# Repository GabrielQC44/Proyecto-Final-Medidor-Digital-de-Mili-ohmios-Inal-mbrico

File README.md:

# Medidor Digital de Mili-ohmios Inalámbrico (IoT)

**Proyecto Final – Diseño de Sistemas Electrónicos**  
*Escuela de Ingenierías Eléctrica, Electrónica y de Telecomunicaciones (E3T)*  
**Universidad Industrial de Santander (UIS)**  
**Grupo:** C1B-A1A  

---

## Autores
* **Gabriel Camilo Quijano Celis** – *Código:* 2192312
* **Carlos Daniel Aguilera Iglesias** – *Código:* 2192318

---

## Descripción del Proyecto

El **Medidor Digital de Mili-ohmios Inalámbrico** es un instrumento de metrología portátil diseñado para medir resistencias de ultra-bajo valor en el rango de **$0.5\,\text{m}\Omega$ a $1000\,\text{m}\Omega$**. 

Fundamentado en el **método de cuatro hilos (Conexión Kelvin)** y **medición ratiométrica**, elimina por completo los errores introducidos por resistencias parásitas de cables, conectores y derivas térmicas por efecto Seebeck. Los datos metrológicos se procesan mediante un microcontrolador ESP32-C3 SuperMini y se transmiten vía **Bluetooth Low Energy (BLE 5)** hacia una interfaz web responsiva e interactiva.

---

## Probar la Aplicación Web (Sin Descargas)

Puedes probar e interactuar con la interfaz gráfica del instrumento directamente desde tu navegador sin instalar nada:  
**[Abrir Aplicación en GitHub Pages](https://gabrielqc44.github.io/Proyecto-Final-Medidor-Digital-de-Mili-ohmios-Inal-mbrico/)**

---

## Arquitectura del Hardware

El hardware se divide en cuatro etapas funcionales integradas en una placa de $7 \times 7\,\text{cm}$:

1. **Etapa 1: Gestión de Alimentación y Carga:** Módulo TP4056 con protección BMS para batería Li-Po 1S y regulador Buck-Boost TPS63802 ($3.3\,\text{V}$ estables).
2. **Etapa 2: Fuente de Corriente Constante y Escalas:** Lazo analógico de precisión (OPA376 + MOSFET IRLZ44N) accionado por un buffer 74LVC1G125 mediante excitación pulsada de $55\,\text{ms}$ ($100\,\text{mA}$, $500\,\text{mA}$ y $1\,\text{A}$).
3. **Etapa 3: Adquisición Analógica de Alta Precisión:** Convertidor $\Delta-\Sigma$ ADS1220 de 24 bits configurado en modo diferencial ratiométrico.
4. **Etapa 4: Control y Comunicaciones:** Microcontrolador ESP32-C3 SuperMini ejecutando el servidor BLE GATT y algoritmos de *Auto-Zeroing* (compensación ON/OFF).

---

## Estructura del Repositorio

| Archivo / Carpeta | Descripción |
| :--- | :--- |
| `esquemas/` | Planos esquemáticos del circuito impreso y documentación técnica. |
| `gerbers/` | Archivos de fabricación Gerber para la manufactura de la placa PCB. |
| `Aplicacion.apk` | Instalador compilado para dispositivos móviles Android. |
| `Codigo_ESP.txt` | Código fuente del firmware en C++ para el microcontrolador ESP32-C3. |
| `Interfazz.html` | Código fuente de la interfaz gráfica web en HTML5, CSS3 y JavaScript. |
| `index.html` | Despliegue de la interfaz web para el servidor de GitHub Pages. |
| `logo.png` | Logotipo oficial e identidad visual del proyecto. |

---

## Características Clave
* **Modo Ratiométrico:** Inmune a fluctuaciones o derivas en la corriente de excitación.
* **Excitación Pulsada ($<10\%$ Ciclo de Trabajo):** Disipa menos de $0.41\,\text{W}$, evitando autocalentamiento en resistencias SMD 2512.
* **Compensación de Offset:** Técnica de dos fases ($V_{\text{ON}} - V_{\text{OFF}}$) que anula tensiones termoeléctricas.
* **Costo-Efectivo:** Construcción total por **$20.40 USD** (~$88\%$ de ahorro frente a equipos comerciales equivalentes).

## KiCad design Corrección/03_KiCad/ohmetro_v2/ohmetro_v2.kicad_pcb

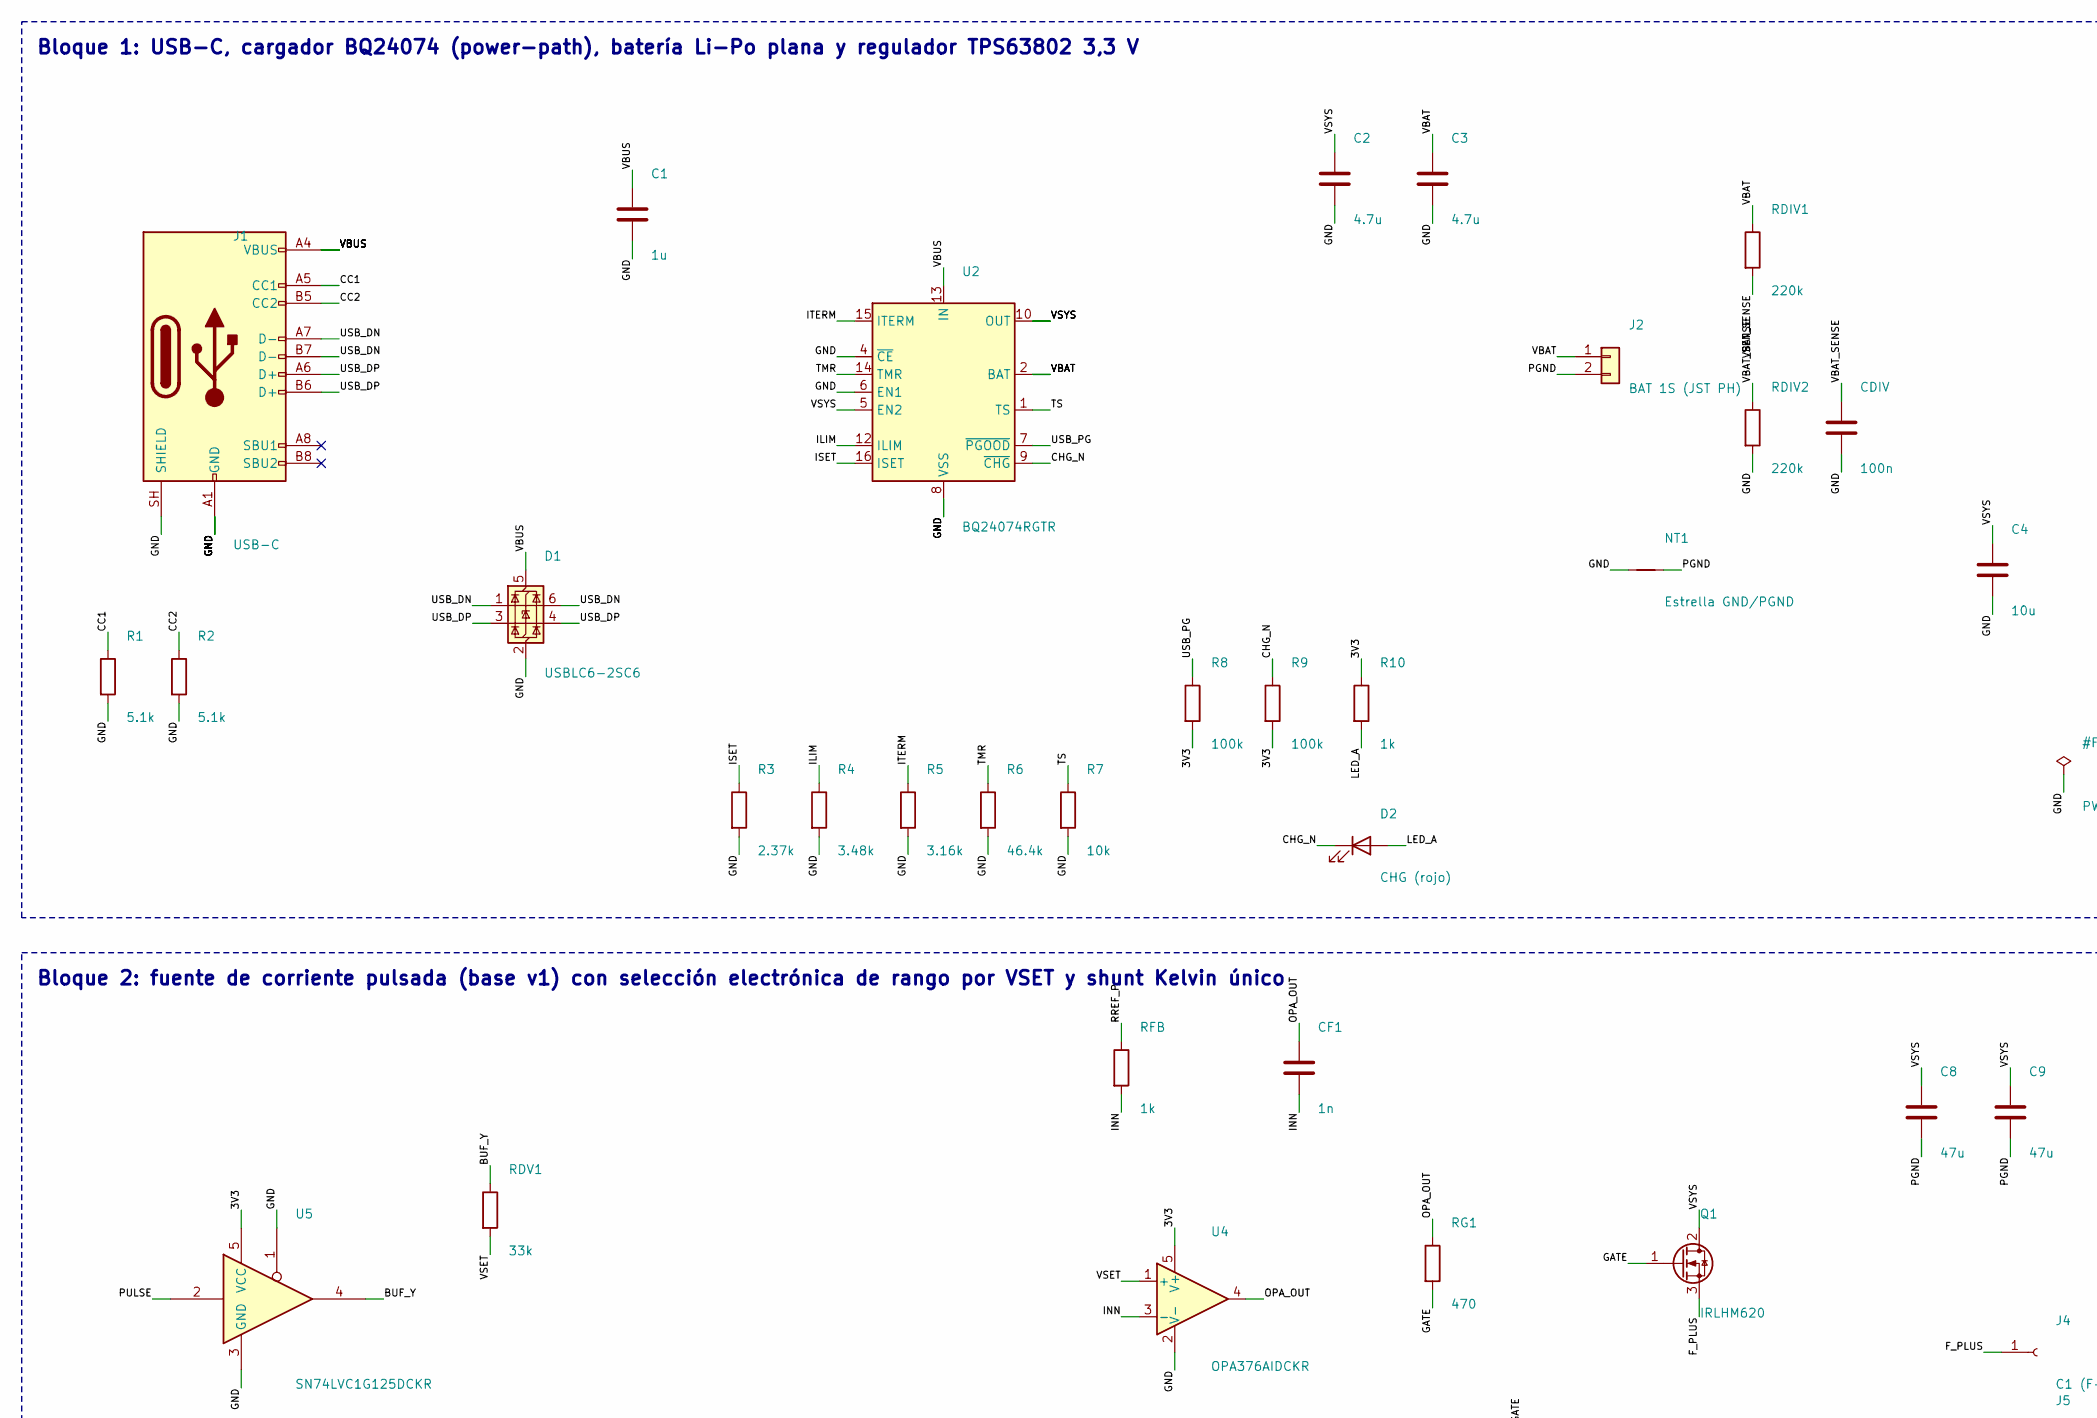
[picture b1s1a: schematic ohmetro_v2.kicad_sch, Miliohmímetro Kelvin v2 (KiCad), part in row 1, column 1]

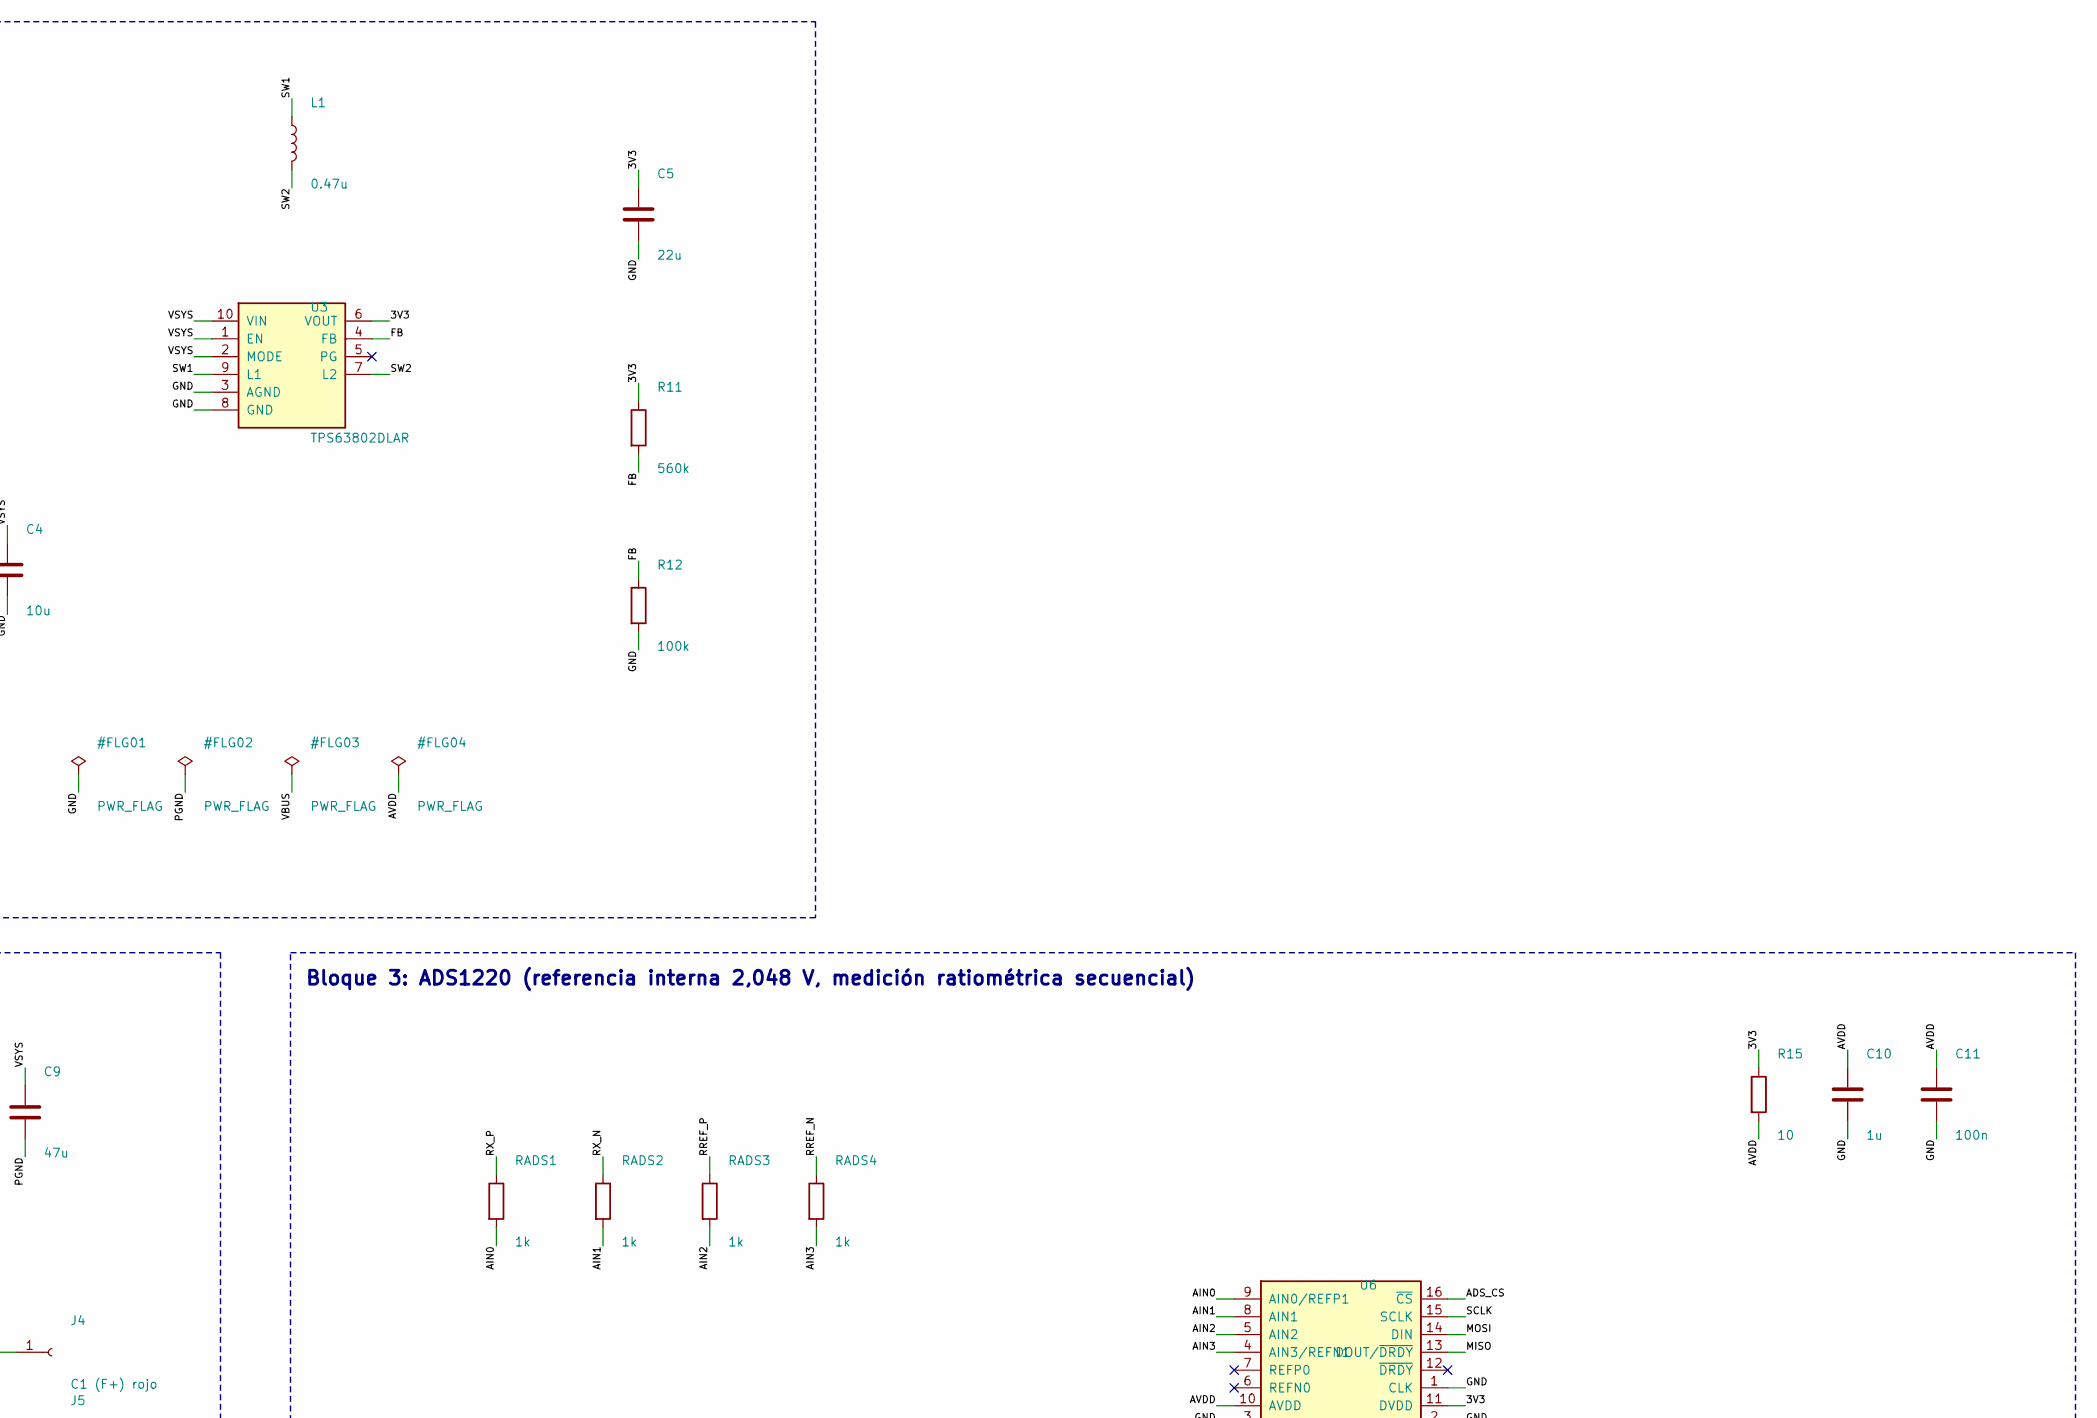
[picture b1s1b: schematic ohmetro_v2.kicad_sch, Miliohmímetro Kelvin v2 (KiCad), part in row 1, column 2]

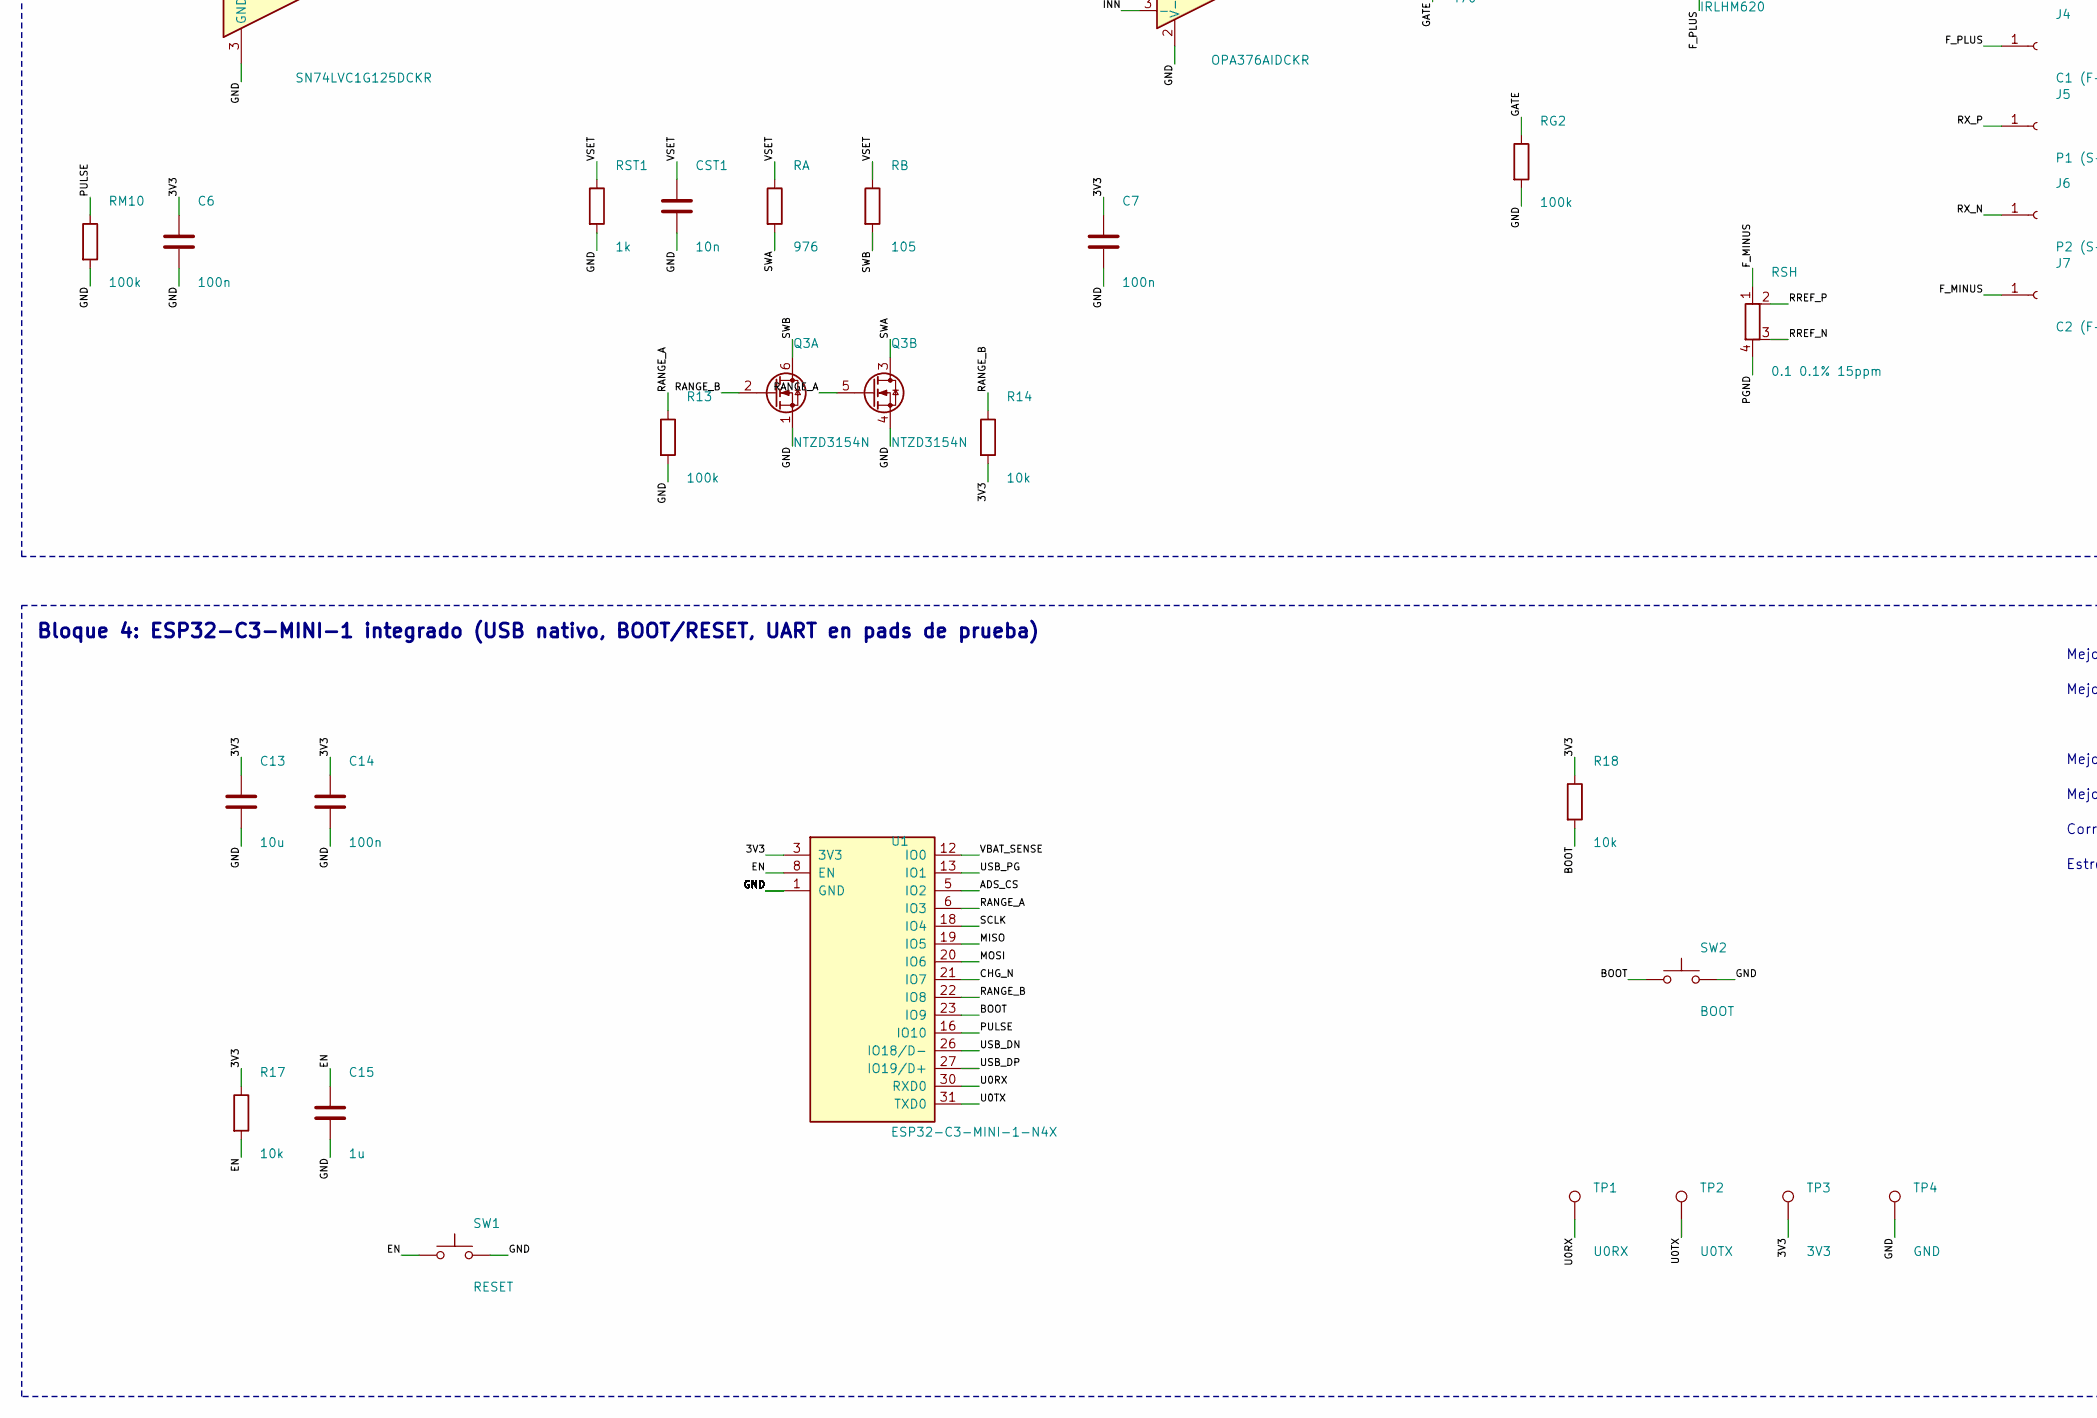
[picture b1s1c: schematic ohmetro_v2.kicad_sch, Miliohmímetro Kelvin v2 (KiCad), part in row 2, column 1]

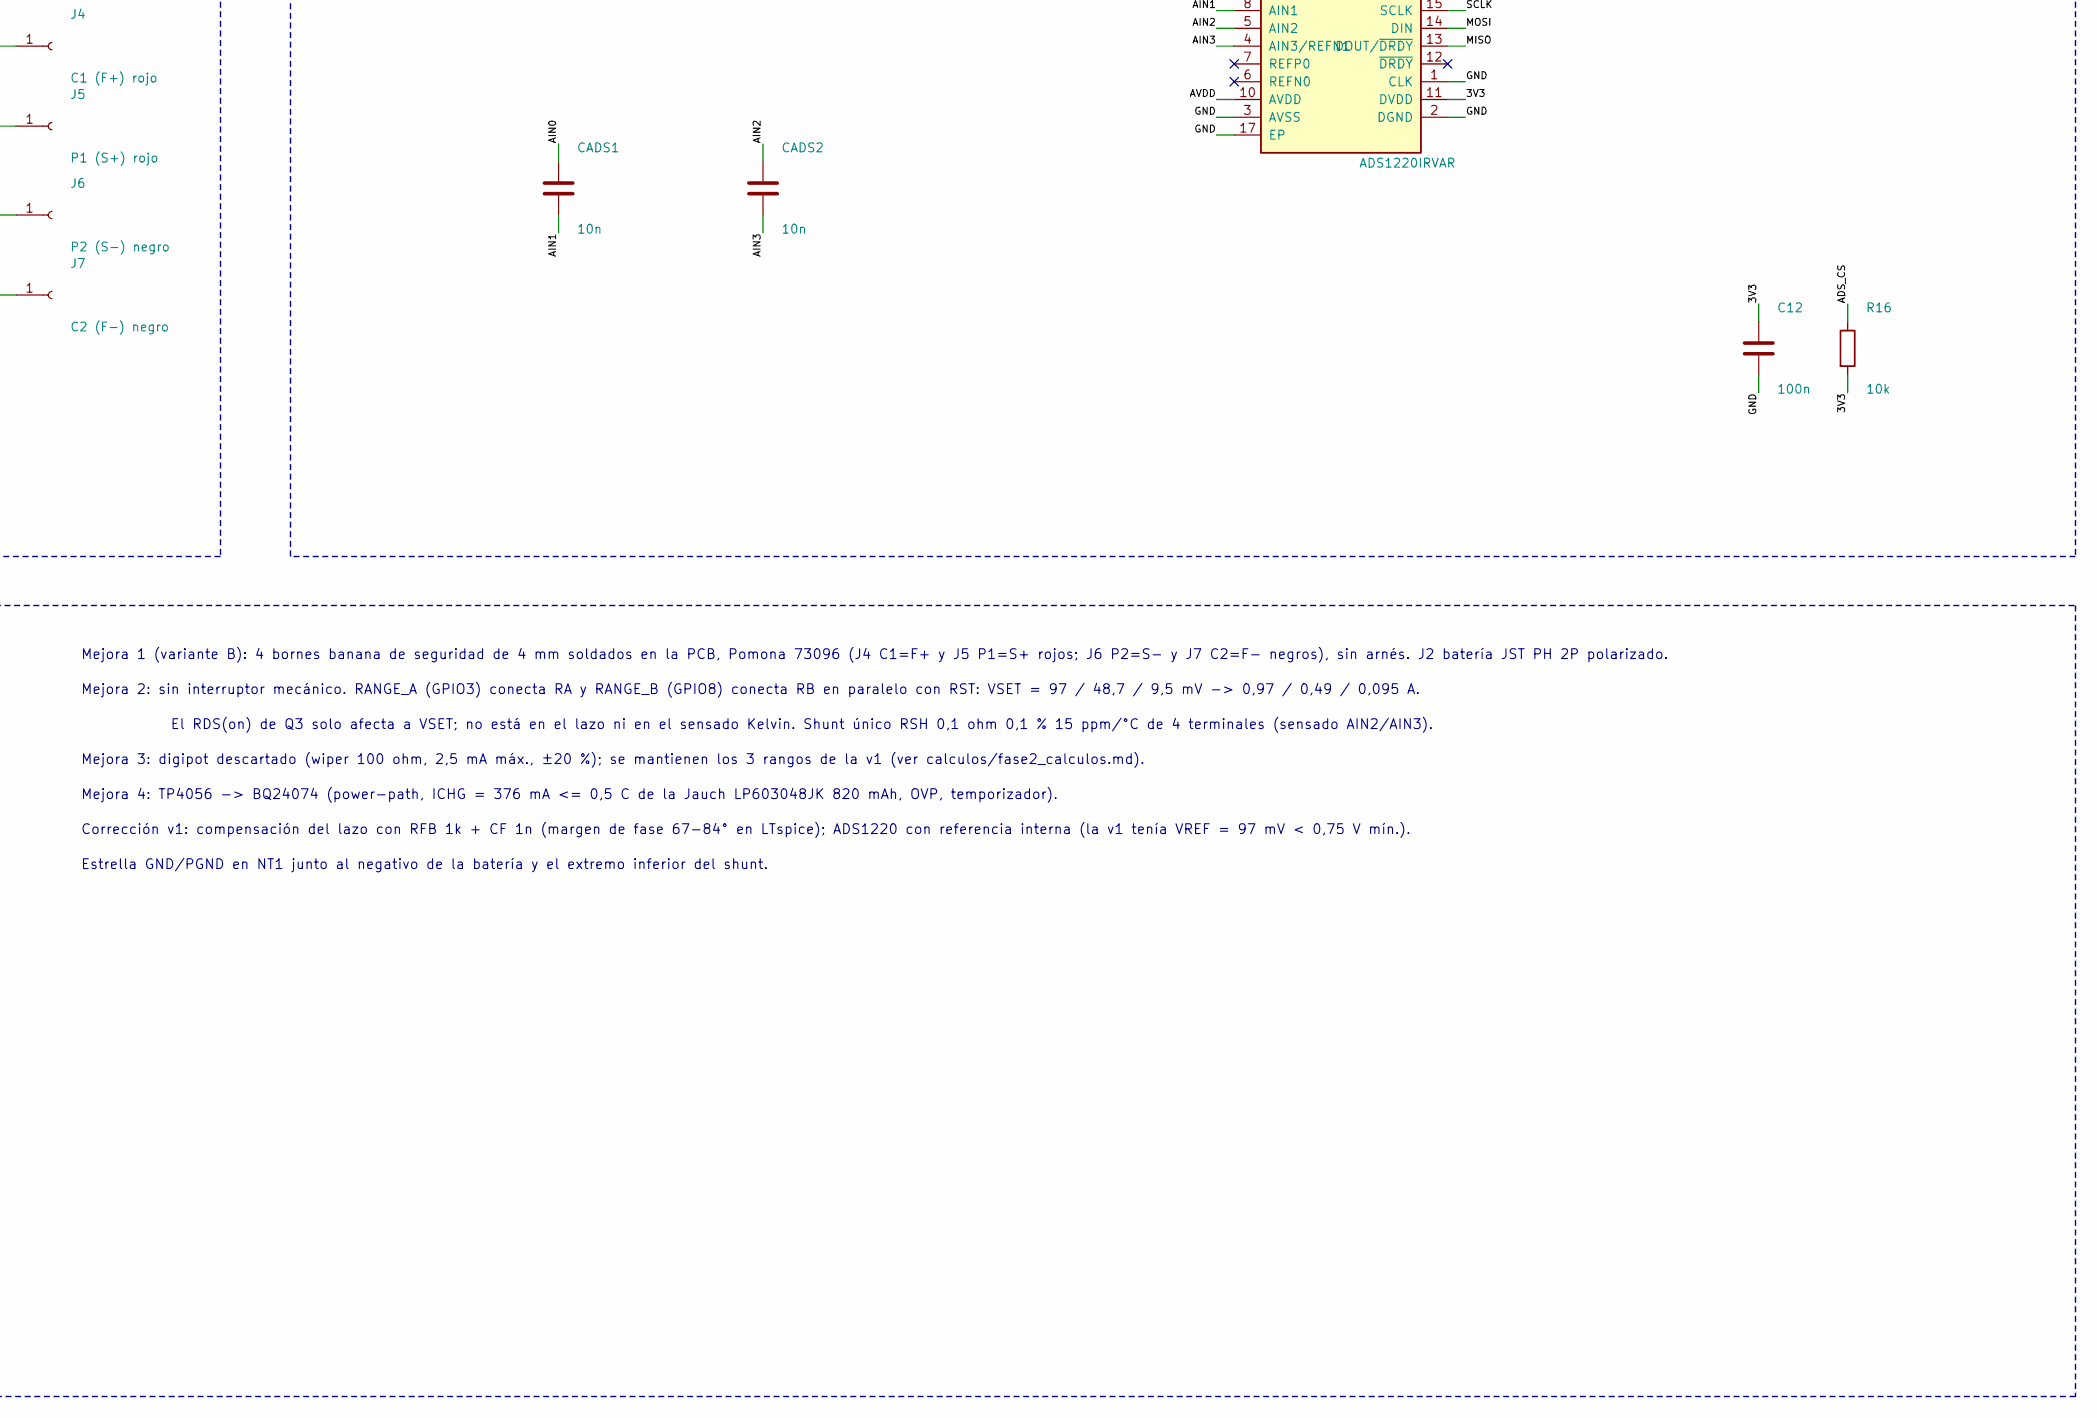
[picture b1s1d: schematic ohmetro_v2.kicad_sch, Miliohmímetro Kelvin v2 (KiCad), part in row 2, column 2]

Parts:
C1, C10, C15: 1u; C_0402_1005Metric; MPN CL05A105KA5NQNC
C2, C3: 4.7u; C_0603_1608Metric; MPN CL10A475KO8NNNC
C4, C13: 10u; C_0603_1608Metric; MPN CL10A106KP8NNNC
C5: 22u; C_0805_2012Metric; MPN GRM21BR61A226ME44L
C6, C7, C11, C12, C14: 100n; C_0402_1005Metric; MPN CL05B104KO5NNNC
C8, C9: 47u; C_0805_2012Metric; MPN CL21A476MQYNNNE
CADS1, CADS2: 10n; C_0603_1608Metric; MPN GRM1885C1H103JA01D
CDIV: 100n; C_0402_1005Metric; MPN CL05B104KO5NNNC
CF1: 1n; C_0402_1005Metric; MPN GRM1555C1H102JA01D
CST1: 10n; C_0603_1608Metric; MPN GRM1885C1H103JA01D
D1: USBLC6-2SC6; SOT-23-6; MPN USBLC6-2SC6
D2: CHG (rojo); LED_0603_1608Metric; MPN LTST-C191KRKT
J1: USB-C; USB_C_Receptacle_GCT_USB4105-xx-A_16P_TopMnt_Horizontal; MPN USB4105-GF-A
J2: BAT 1S (JST PH); JST_PH_S2B-PH-SM4-TB_1x02-1MP_P2.00mm_Horizontal; MPN S2B-PH-SM4-TB(LF)(SN)
J4: C1 (F+) rojo; Pomona_73096_4mm_Vertical; MPN 73096-2
J5: P1 (S+) rojo; Pomona_73096_4mm_Vertical; MPN 73096-2
J6: P2 (S-) negro; Pomona_73096_4mm_Vertical; MPN 73096-0
J7: C2 (F-) negro; Pomona_73096_4mm_Vertical; MPN 73096-0
L1: 0.47u; L_Murata_DFE201610P; MPN DFE201612E-R47M=P2
NT1: Estrella GND/PGND; NetTie-2_SMD_Pad0.5mm
Q1: IRLHM620; Infineon_PQFN-8_3.3x3.3mm; MPN IRLHM620TRPBF
Q3: NTZD3154N; SOT-563; MPN NTZD3154NT1G
R1, R2: 5.1k; R_0402_1005Metric; MPN RC0402FR-075K1L
R3: 2.37k; R_0402_1005Metric; MPN RC0402FR-072K37L
R4: 3.48k; R_0402_1005Metric; MPN RC0402FR-073K48L
R5: 3.16k; R_0402_1005Metric; MPN RC0402FR-073K16L
R6: 46.4k; R_0402_1005Metric; MPN RC0402FR-0746K4L
R7, R14, R16, R17, R18: 10k; R_0402_1005Metric; MPN RC0402FR-0710KL
R8, R9, R12, R13: 100k; R_0402_1005Metric; MPN RC0402FR-07100KL
R10: 1k; R_0402_1005Metric; MPN RC0402FR-071KL
R11: 560k; R_0402_1005Metric; MPN RC0402FR-07560KL
R15: 10; R_0402_1005Metric; MPN RC0402FR-0710RL
RA: 976; R_0402_1005Metric; MPN RC0402FR-07976RL
RADS1, RADS2, RADS3, RADS4: 1k; R_0402_1005Metric; MPN ERA-2AEB102X
RB: 105; R_0402_1005Metric; MPN RC0402FR-07105RL
RDIV1, RDIV2: 220k; R_0402_1005Metric; MPN RC0402FR-07220KL
RDV1: 33k; R_0402_1005Metric; MPN RC0402FR-0733KL
RFB: 1k; R_0402_1005Metric; MPN RC0402FR-071KL
RG1: 470; R_0402_1005Metric; MPN RC0402FR-07470RL
RG2: 100k; R_0402_1005Metric; MPN RC0402FR-07100KL
RM10: 100k; R_0402_1005Metric; MPN RC0402FR-07100KL
RSH: 0.1 0.1% 15ppm; R_Shunt_VPG_CSM2512S_4T; MPN Y44870R10000B9R
RST1: 1k; R_0402_1005Metric; MPN RC0402FR-071KL
SW1: RESET; SW_SPST_PTS810; MPN PTS815SJM250SMTRLFS
SW2: BOOT; SW_SPST_PTS810; MPN PTS815SJM250SMTRLFS
TP1: U0RX; TestPoint_Pad_D1.0mm
TP2: U0TX; TestPoint_Pad_D1.0mm
TP3: 3V3; TestPoint_Pad_D1.0mm
TP4: GND; TestPoint_Pad_D1.0mm
U1: ESP32-C3-MINI-1-N4X; ESP32-C3-MINI-1; MPN ESP32-C3-MINI-1-N4X
U2: BQ24074RGTR; VQFN-16-1EP_3x3mm_P0.5mm_EP1.68x1.68mm_ThermalVias; MPN BQ24074RGTR
U3: TPS63802DLAR; TI_DLA_VSON-HR-10_2x3mm; MPN TPS63802DLAR
U4: OPA376AIDCKR; SOT-353_SC-70-5; MPN OPA376AIDCKR
U5: SN74LVC1G125DCKR; SOT-353_SC-70-5; MPN SN74LVC1G125DCKR
U6: ADS1220IRVAR; Texas_RVA_VQFN-16-1EP_3.5x3.5mm_P0.5mm_EP2.14x2.14mm; MPN ADS1220IRVAR

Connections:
/3V3: C5.1, C6.1, C7.1, C12.1, C13.1, C14.1, R8.2, R9.2, R10.1, R11.1, R14.2, R15.1, R16.2, R17.1, R18.1, TP3.1, U1.3 (3V3), U3.6 (VOUT), U4.5 (V+), U5.5 (VCC), U6.11 (DVDD)
/ADS_CS: R16.1, U1.5 (IO2), U6.16 (~CS)
/AIN0: CADS1.1, RADS1.2, U6.9 (AIN0/REFP1)
/AIN1: CADS1.2, RADS2.2, U6.8 (AIN1)
/AIN2: CADS2.1, RADS3.2, U6.5 (AIN2)
/AIN3: CADS2.2, RADS4.2, U6.4 (AIN3/REFN1)
/AVDD: C10.1, C11.1, R15.2, U6.10 (AVDD)
/BOOT: R18.2, SW2.1, U1.23 (IO9)
/BUF_Y: RDV1.1, U5.4
/CC1: J1.A5 (CC1), R1.1
/CC2: J1.B5 (CC2), R2.1
/CHG_N: D2.1 (K), R9.1, U1.21 (IO7), U2.9 (~CHG)
/EN: C15.1, R17.2, SW1.1, U1.8 (EN)
/FB: R11.2, R12.1, U3.4 (FB)
/F_MINUS: J7.1, RSH.1
/F_PLUS: J4.1, Q1.3 (S)
/GATE: Q1.1 (G), RG1.2, RG2.1
/ILIM: R4.1, U2.12 (ILIM)
/INN: CF1.2, RFB.2, U4.3 (-)
/ISET: R3.1, U2.16 (ISET)
/ITERM: R5.1, U2.15 (ITERM)
/LED_A: D2.2 (A), R10.2
/MISO: U1.19 (IO5), U6.13 (DOUT/~DRDY)
/MOSI: U1.20 (IO6), U6.14 (DIN)
/OPA_OUT: CF1.1, RG1.1, U4.4
/PGND: C8.2, C9.2, J2.2, NT1.2, RSH.4
/PULSE: RM10.1, U1.16 (IO10), U5.2
/RANGE_A: Q3.5 (G), R13.1, U1.6 (IO3)
/RANGE_B: Q3.2 (G), R14.1, U1.22 (IO8)
/RREF_N: RADS4.1, RSH.3
/RREF_P: RADS3.1, RFB.1, RSH.2
/RX_N: J6.1, RADS2.1
/RX_P: J5.1, RADS1.1
/SCLK: U1.18 (IO4), U6.15 (SCLK)
/SW1: L1.1, U3.9 (L1)
/SW2: L1.2, U3.7 (L2)
/SWA: Q3.3 (D), RA.2
/SWB: Q3.6 (D), RB.2
/TMR: R6.1, U2.14 (TMR)
/TS: R7.1, U2.1 (TS)
/U0RX: TP1.1, U1.30 (RXD0)
/U0TX: TP2.1, U1.31 (TXD0)
/USB_DN: D1.1 (I/O1), D1.6 (I/O1), J1.A7 (D-), J1.B7 (D-), U1.26 (IO18/D-)
/USB_DP: D1.3 (I/O2), D1.4 (I/O2), J1.A6 (D+), J1.B6 (D+), U1.27 (IO19/D+)
/USB_PG: R8.1, U1.13 (IO1), U2.7 (~PGOOD)
/VBAT: C3.1, J2.1, RDIV1.1, U2.2 (BAT), U2.3 (BAT)
/VBAT_SENSE: CDIV.1, RDIV1.2, RDIV2.1, U1.12 (IO0)
/VBUS: C1.1, D1.5 (VBUS), J1.A4 (VBUS), J1.A9 (VBUS), J1.B4 (VBUS), J1.B9 (VBUS), U2.13 (IN)
/VSET: CST1.1, RA.1, RB.1, RDV1.2, RST1.1, U4.1 (+)
/VSYS: C2.1, C4.1, C8.1, C9.1, Q1.2 (D), U2.5 (EN2), U2.10 (OUT), U2.11 (OUT), U3.1 (EN), U3.2 (MODE), U3.10 (VIN)
GND: C1.2, C2.2, C3.2, C4.2, C5.2, C6.2, C7.2, C10.2, C11.2, C12.2, C13.2, C14.2, C15.2, CDIV.2, CST1.2, D1.2 (GND), J1.A1 (GND), J1.A12 (GND), J1.B1 (GND), J1.B12 (GND), J1.SH (SHIELD), NT1.1, Q3.1 (S), Q3.4 (S), R1.2, R2.2, R3.2, R4.2, R5.2, R6.2, R7.2, R12.2, R13.2, RDIV2.2, RG2.2, RM10.2, RST1.2, SW1.2, SW2.2, TP4.1, U1.1 (GND), U1.2 (GND), U1.11 (GND), U1.14 (GND), U1.36 (GND), U1.37 (GND), U1.38 (GND), U1.39 (GND), U1.40 (GND), U1.41 (GND), U1.42 (GND), U1.43 (GND), U1.44 (GND), U1.45 (GND), U1.46 (GND), U1.47 (GND), U1.48 (GND), U1.49 (GND), U1.50 (GND), U1.51 (GND), U1.52 (GND), U1.53 (GND), U2.4 (~CE), U2.6 (EN1), U2.8 (VSS), U2.17 (VSS), U3.3 (AGND), U3.8 (GND), U4.2 (V-), U5.1, U5.3 (GND), U6.1 (CLK), U6.2 (DGND), U6.3 (AVSS), U6.17 (EP)

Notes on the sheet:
Bloque 1: USB-C, cargador BQ24074 (power-path), batería Li-Po plana y regulador TPS63802 3,3 V
Bloque 2: fuente de corriente pulsada (base v1) con selección electrónica de rango por VSET y shunt Kelvin único
Bloque 3: ADS1220 (referencia interna 2,048 V, medición ratiométrica secuencial)
Bloque 4: ESP32-C3-MINI-1 integrado (USB nativo, BOOT/RESET, UART en pads de prueba)
Mejora 1 (variante B): 4 bornes banana de seguridad de 4 mm soldados en la PCB, Pomona 73096 (J4 C1=F+ y J5 P1=S+ rojos; J6 P2=S- y J7 C2=F- negros), sin arnés. J2 batería JST PH 2P polarizado.
Mejora 2: sin interruptor mecánico. RANGE_A (GPIO3) conecta RA y RANGE_B (GPIO8) conecta RB en paralelo con RST: VSET = 97 / 48,7 / 9,5 mV -> 0,97 / 0,49 / 0,095 A.
El RDS(on) de Q3 solo afecta a VSET; no está en el lazo ni en el sensado Kelvin. Shunt único RSH 0,1 ohm 0,1 % 15 ppm/°C de 4 terminales (sensado AIN2/AIN3).
Mejora 3: digipot descartado (wiper 100 ohm, 2,5 mA máx., ±20 %); se mantienen los 3 rangos de la v1 (ver calculos/fase2_calculos.md).
Mejora 4: TP4056 -> BQ24074 (power-path, ICHG = 376 mA <= 0,5 C de la Jauch LP603048JK 820 mAh, OVP, temporizador).
Corrección v1: compensación del lazo con RFB 1k + CF 1n (margen de fase 67-84° en LTspice); ADS1220 con referencia interna (la v1 tenía VREF = 97 mV < 0,75 V mín.).
Estrella GND/PGND en NT1 junto al negativo de la batería y el extremo inferior del shunt.

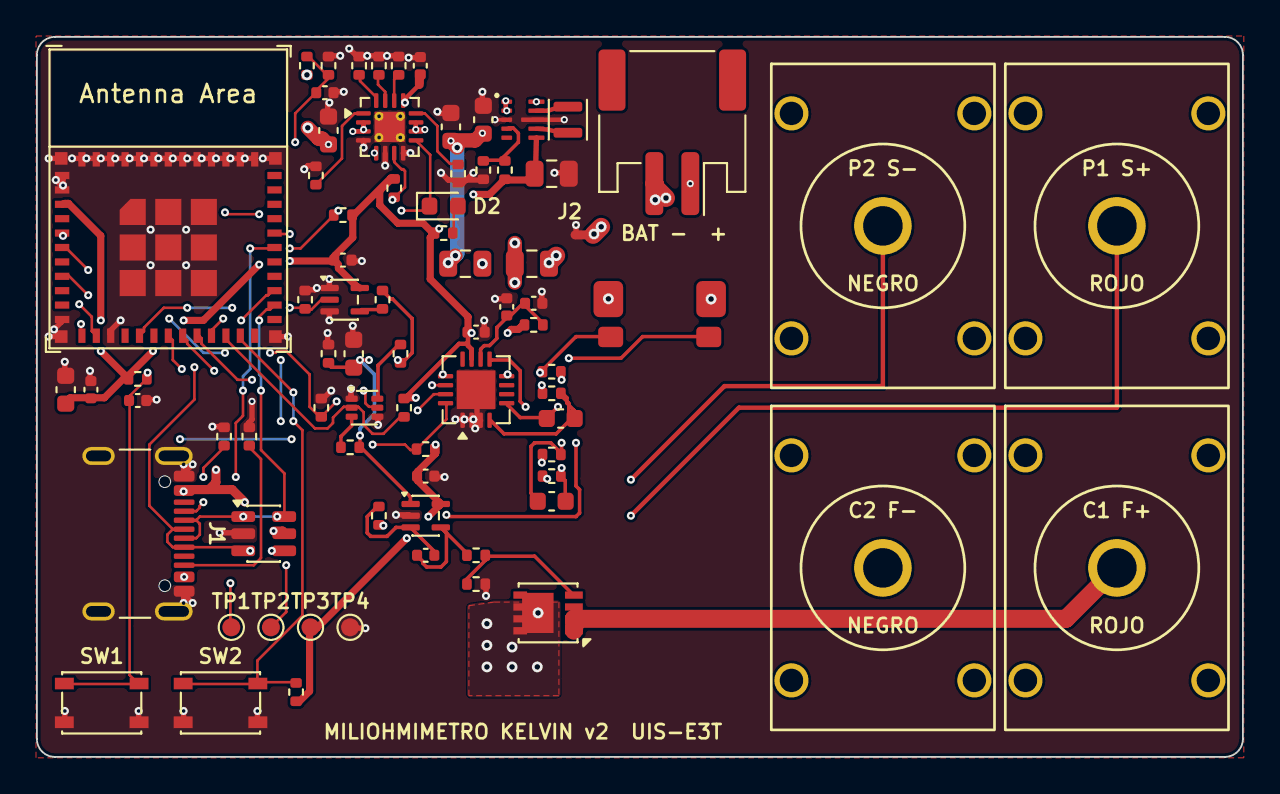
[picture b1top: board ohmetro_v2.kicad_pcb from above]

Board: 4 copper layers, 67.0 x 40.0 mm, 77 parts (0 on the bottom side), 51 nets.

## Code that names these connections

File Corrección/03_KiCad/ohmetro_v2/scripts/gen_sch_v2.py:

# -*- coding: utf-8 -*-
"""Genera ohmetro_v2.kicad_sch (mejoras 1–4 y ESP32-C3-MINI-1 integrado) y la biblioteca ohmetro.kicad_sym."""
import os, sys
HERE = os.path.dirname(os.path.abspath(__file__))
sys.path.insert(0, HERE); sys.path.insert(0, os.path.join(HERE, "..", "..", "tools"))
from kicad_sch_lib import Sheet, flat_symbol
import design_v2 as D

OUT = os.path.join(HERE, "..")

def sym_box(name, left, right, ref="U", width=20.32, stack_names=("GND",)):
    """Símbolo rectangular; pines con nombre en stack_names se apilan (uno visible)."""
    def side(lst, x, ang):
        out, slot, stacked = [], 0, {}
        for num, nm, typ in lst:
            if nm in stack_names and nm in stacked:
                y = stacked[nm]; hide = " hide"
            else:
                y = -2.54 * slot; slot += 1; stacked[nm] = y; hide = ""
            out.append((num, nm, typ, x, y, ang, hide))
        return out, slot
    L, nl = side(left, -width / 2 - 3.81, 0)
    R, nr = side(right, width / 2 + 3.81, 180)
    n = max(nl, nr)
    top = 2.54; bot = -2.54 * n
    pins = []
    for num, nm, typ, x, y, ang, hide in L + R:
        y += 2.54 * ((n - 1) // 2)
        y = round(y / 1.27) * 1.27
        pins.append(f'(pin {typ} line (at {x:.2f} {y:.2f} {ang}) (length 3.81){hide} '
                    f'(name "{nm}" (effects (font (size 1.27 1.27)))) (number "{num}" (effects (font (size 1.27 1.27)))))')
    ytop = 2.54 * ((n - 1) // 2) + 2.54
    ybot = ytop - 2.54 * (n + 1)
    return f'''(symbol "ohmetro:{name}" (pin_names (offset 1.016)) (exclude_from_sim no) (in_bom yes) (on_board yes)
      (property "Reference" "{ref}" (at 0 {ytop + 2.54:.2f} 0) (effects (font (size 1.27 1.27))))
      (property "Value" "{name}" (at 0 {ybot - 2.54:.2f} 0) (effects (font (size 1.27 1.27))))
      (property "Footprint" "" (at 0 0 0) (effects (font (size 1.27 1.27)) (hide yes)))
      (property "Datasheet" "" (at 0 0 0) (effects (font (size 1.27 1.27)) (hide yes)))
      (property "Description" "" (at 0 0 0) (effects (font (size 1.27 1.27)) (hide yes)))
      (symbol "{name}_0_1" (rectangle (start {-width/2:.2f} {ytop:.2f}) (end {width/2:.2f} {ybot:.2f})
          (stroke (width 0.254) (type default)) (fill (type background))))
      (symbol "{name}_1_1" {" ".join(pins)}))'''

sh = Sheet("ohmetro_v2", "Miliohmímetro Kelvin v2 (KiCad)", paper="A2")
for lib, name in [("Device", "R"), ("Device", "C"), ("Device", "L"), ("Device", "LED"), ("Device", "R_Shunt"),
                  ("Device", "NetTie_2"), ("Connector", "USB_C_Receptacle_USB2.0_16P"), ("Connector", "TestPoint"),
                  ("Connector_Generic", "Conn_01x02"), ("Connector_Generic", "Conn_01x04"), ("Connector", "Conn_01x01_Socket"),
                  ("Power_Protection", "USBLC6-2SC6"), ("Battery_Management", "BQ24074RGT"),
                  ("74xGxx", "SN74LVC1G125DCK"), ("Amplifier_Operational", "OPA376xxDCK"),
                  ("Transistor_FET", "Q_NMOS_GDS"), ("Transistor_FET", "Q_Dual_NMOS_S1G1D2S2G2D1"),
                  ("Switch", "SW_Push"), ("power", "PWR_FLAG")]:
    sh.add_lib(f"{lib}:{name}", flat_symbol(lib, name))
custom = {
    "ADS1220_RVA": sym_box("ADS1220_RVA", *D.ADS1220_RVA_PINS, width=22.86, stack_names=()),
    "TPS63802DLA": sym_box("TPS63802DLA", *D.TPS63802_PINS, width=15.24, stack_names=()),
    "ESP32-C3-MINI-1": sym_box("ESP32-C3-MINI-1", D.ESP_LEFT[:3] + D.ESP_LEFT[3:len(D.GNDP) + 2], D.ESP_RIGHT, width=17.78),
}
for k, v in custom.items():
    sh.add_lib(f"ohmetro:{k}", v)
open(os.path.join(OUT, "ohmetro.kicad_sym"), "w", encoding="utf-8").write(
    '(kicad_symbol_lib (version 20231120) (generator "ohmetro_scripts")\n' +
    "\n".join(v.replace(f'(symbol "ohmetro:{k}"', f'(symbol "{k}"', 1) for k, v in custom.items()) + "\n)\n")

# pines del OPA376 (DCK) por nombre
from kicad_sch_lib import pins_of
# ESP32: los NC no están en el símbolo
lib, val, fp, nets, mpn, unit = D.P["U1"]
D.P["U1"] = (lib, val, fp, {k: v for k, v in nets.items() if k not in D.NCP}, mpn, unit)

POS = {
 # Bloque 1 (A2 = 594 x 420 mm)
 "J1": (35, 70), "R1": (20, 115), "R2": (30, 115), "D1": (80, 105), "U2": (140, 75), "C1": (95, 50),
 "C2": (195, 45), "C3": (210, 45), "R3": (110, 135), "R4": (122, 135), "R5": (134, 135), "R6": (146, 135),
 "R7": (158, 135), "R8": (175, 120), "R9": (187, 120), "R10": (199, 120), "D2": (199, 140),
 "J2": (235, 70), "RDIV1": (255, 55), "RDIV2": (255, 80), "CDIV": (268, 80), "NT1": (240, 100),
 "U3": (330, 70), "L1": (330, 40), "C4": (290, 100), "C5": (380, 50), "R11": (380, 80), "R12": (380, 105),
 # Bloque 2 (flujo de señal, con cables)
 "U5": (45, 205), "C6": (30, 240), "RM10": (18, 240), "RDV1": (75, 192), "RST1": (90, 235), "CST1": (102, 235),
 "RA": (116, 235), "RB": (130, 235), "Q3": (116, 262), "Q3B": (130, 262), "R13": (100, 268), "R14": (146, 268),
 "U4": (175, 205), "C7": (163, 240), "RFB": (165, 172), "CF1": (190, 172), "RG1": (210, 200), "RG2": (222, 228),
 "Q1": (245, 200), "C8": (280, 178), "C9": (292, 178), "J4": (296, 212), "J5": (296, 224), "J6": (296, 236), "J7": (296, 248), "RSH": (255, 252),
 # Bloque 3
 "U6": (480, 215), "RADS1": (360, 190), "RADS2": (375, 190), "RADS3": (390, 190), "RADS4": (405, 190),
 "CADS1": (368, 232), "CADS2": (398, 232), "R15": (540, 175), "C10": (553, 175), "C11": (565, 175),
 "C12": (540, 255), "R16": (553, 255),
 # Bloque 4
 "U1": (130, 345), "C13": (40, 320), "C14": (52, 320), "R17": (40, 365), "C15": (52, 365), "SW1": (70, 385),
 "R18": (230, 320), "SW2": (245, 345), "TP1": (230, 380), "TP2": (245, 380), "TP3": (260, 380), "TP4": (275, 380),
}
sh.wired = set()   # redibujo con cables pendiente (unía redes); se usa la versión con etiquetas verificada
for ref, (lib_id, val, fp, nets, mpn, unit) in D.P.items():
    x, y = POS[ref]
    sh.place(lib_id, ref[:-1] if ref == "Q3B" else ref, val, fp, x, y, nets, mpn, unit=unit,
             in_bom=not (ref.startswith("TP") or ref.startswith("NT")), on_board=ref not in D.OFF_BOARD)
sh.connect_wired()
for i, (net, x, y) in enumerate([("GND", 300, 130), ("PGND", 315, 130), ("VBUS", 330, 130), ("AVDD", 345, 130)]):
    sh.place("power:PWR_FLAG", f"#FLG0{i+1}", "PWR_FLAG", "", x, y, {"1": net})

for (x1, y1, x2, y2, t) in [(8, 22, 405, 150, "Bloque 1: USB-C, cargador BQ24074 (power-path), batería Li-Po plana y regulador TPS63802 3,3 V"),
                            (8, 155, 320, 285, "Bloque 2: fuente de corriente pulsada (base v1) con selección electrónica de rango por VSET y shunt Kelvin único"),
                            (330, 155, 585, 285, "Bloque 3: ADS1220 (referencia interna 2,048 V, medición ratiométrica secuencial)"),
                            (8, 292, 585, 405, "Bloque 4: ESP32-C3-MINI-1 integrado (USB nativo, BOOT/RESET, UART en pads de prueba)")]:
    sh.rect(x1, y1, x2, y2); sh.text(t, x1 + 2, y1 + 5, 2.0)
notes = ["Mejora 1 (variante B): 4 bornes banana de seguridad de 4 mm soldados en la PCB, Pomona 73096 (J4 C1=F+ y J5 P1=S+ rojos; J6 P2=S- y J7 C2=F- negros), sin arnés. J2 batería JST PH 2P polarizado.",
         "Mejora 2: sin interruptor mecánico. RANGE_A (GPIO3) conecta RA y RANGE_B (GPIO8) conecta RB en paralelo con RST: VSET = 97 / 48,7 / 9,5 mV -> 0,97 / 0,49 / 0,095 A.",
         "            El RDS(on) de Q3 solo afecta a VSET; no está en el lazo ni en el sensado Kelvin. Shunt único RSH 0,1 ohm 0,1 % 15 ppm/°C de 4 terminales (sensado AIN2/AIN3).",
         "Mejora 3: digipot descartado (wiper 100 ohm, 2,5 mA máx., ±20 %); se mantienen los 3 rangos de la v1 (ver calculos/fase2_calculos.md).",
         "Mejora 4: TP4056 -> BQ24074 (power-path, ICHG = 376 mA <= 0,5 C de la Jauch LP603048JK 820 mAh, OVP, temporizador).",
         "Corrección v1: compensación del lazo con RFB 1k + CF 1n (margen de fase 67-84° en LTspice); ADS1220 con referencia interna (la v1 tenía VREF = 97 mV < 0,75 V mín.).",
         "Estrella GND/PGND en NT1 junto al negativo de la batería y el extremo inferior del shunt."]
for i, n in enumerate(notes):
    sh.text(n, 335, 26 + i * 6 if False else 290 + 0 * i, 1.4, bold=False) if False else None
for i, n in enumerate(notes):
    sh.text(n, 10, 410 + 0 if False else 288 + 0, 1.4, bold=False) if False else None
y0 = 300
for i, n in enumerate(notes):
    sh.text(n, 300, y0 + i * 5, 1.4, bold=False)
sh.write(os.path.join(OUT, "ohmetro_v2.kicad_sch"), "2026-11-09", "2.0 (Fase 2)", "UIS - E3T - Grupo C1B-A1A")
print("ok")

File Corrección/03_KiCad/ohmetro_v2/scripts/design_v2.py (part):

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P["U5"] = ("74xGxx:SN74LVC1G125DCK", "SN74LVC1G125DCKR", "Package_TO_SOT_SMD:SOT-353_SC-70-5",
           {"1": "GND", "2": "PULSE", "3": "GND", "4": "BUF_Y", "5": "3V3"}, "SN74LVC1G125DCKR", 1)
P["C6"] = C("3V3", "GND", "100n", "CL05B104KO5NNNC")
P["RM10"] = R("PULSE", "GND", "100k", Y("100K"))                           # pull-down de GPIO10 (informe v1)
P["RDV1"] = R("BUF_Y", "VSET", "33k", Y("33K"))                            # = v1
P["RST1"] = R("VSET", "GND", "1k", Y("1K"))                                # = v1
P["CST1"] = C("VSET", "GND", "10n", "GRM1885C1H103JA01D", C0603)          # = v1 (C0G)
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P["Q3B"] = ("Transistor_FET:Q_Dual_NMOS_S1G1D2S2G2D1", "NTZD3154N", "Package_TO_SOT_SMD:SOT-563",
            {"4": "GND", "5": "RANGE_A", "3": "SWA"}, "NTZD3154NT1G", 2)
P["R13"] = R("RANGE_A", "GND", "100k", Y("100K"))
P["R14"] = R("RANGE_B", "3V3", "10k", Y("10K"))                            # GPIO8 strapping = 1
P["U4"] = ("Amplifier_Operational:OPA376xxDCK", "OPA376AIDCKR", "Package_TO_SOT_SMD:SOT-353_SC-70-5",
           {"1": "VSET", "2": "GND", "3": "INN", "4": "OPA_OUT", "5": "3V3"}, "OPA376AIDCKR", 1)  # DCK: 1 +IN, 2 V-, 3 -IN, 4 OUT, 5 V+
P["C7"] = C("3V3", "GND", "100n", "CL05B104KO5NNNC")
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P["C10"] = C("AVDD", "GND", "1u", "CL05A105KA5NQNC")
P["C11"] = C("AVDD", "GND", "100n", "CL05B104KO5NNNC")
P["C12"] = C("3V3", "GND", "100n", "CL05B104KO5NNNC")                      # DVDD
P["R16"] = R("ADS_CS", "3V3", "10k", Y("10K"))                             # CS inactivo + strapping GPIO2

# ============================================================ Bloque 4: ESP32-C3-MINI-1 integrado
GNDP = ["1", "2", "11", "14"] + [str(i) for i in range(36, 54)]
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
